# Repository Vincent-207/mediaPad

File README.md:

# mediaPad

This is my submission for hackpad. It's a macropad centered around media control, a mediaPad!
# Features
- 3 keyboard buttons
- One EC11 rotary encoder with a press button
- control of volume, pause/play, stop, skip forward, skip backward.

# PCB & Schematic

This was my first time using kiCAD or any PCB/Schematic design software.
It was unexpectedly pretty easy and the features were a lot more advanced that I was expecting. 

# CAD
This all fit's together with four m3 bolts & nuts that I will supply myself.

# BOM
- 1 XIAO RP2040
- 4x cherry mx red
- 4x DSA Keycaps
- 4x M3x16mm Bolts
- 4x M3 Nylock Nuts
- 1x EC11 Rotary Encoder
- 1x Case (2 3D printed parts)

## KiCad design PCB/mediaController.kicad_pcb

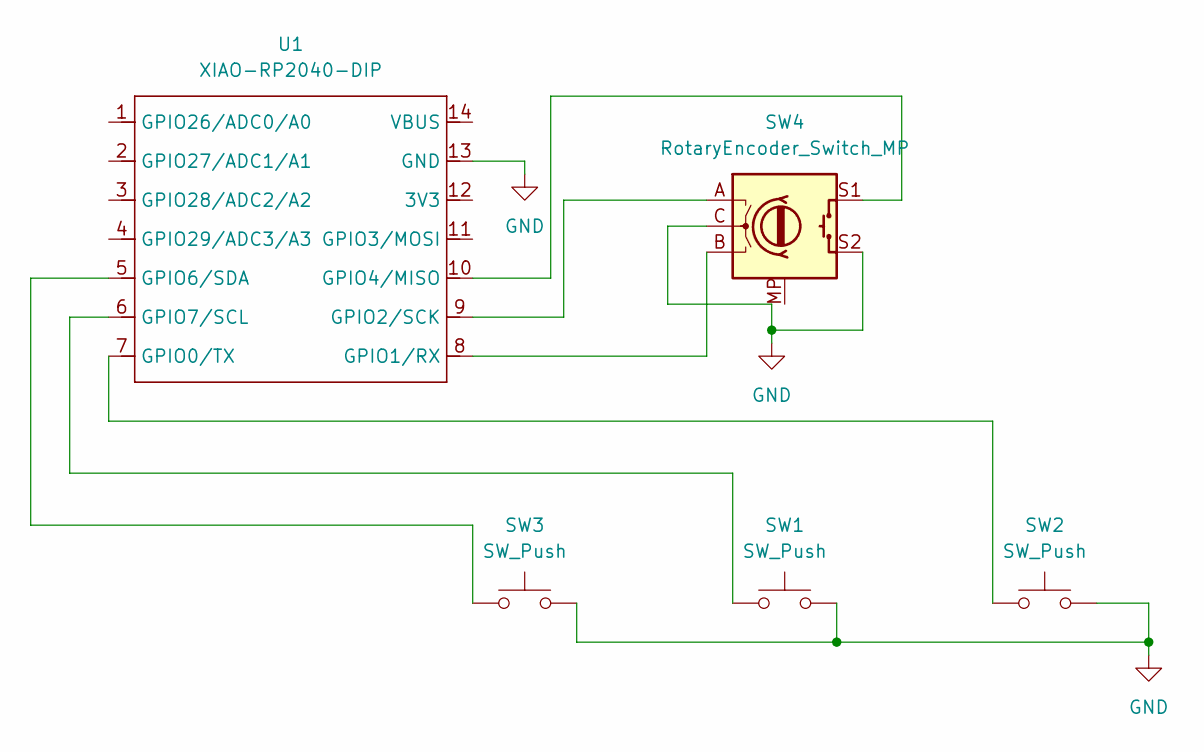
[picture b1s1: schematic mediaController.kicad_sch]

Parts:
SW1, SW2, SW3: SW_Push; SW_Cherry_MX_1.00u_PCB
SW4: RotaryEncoder_Switch_MP; RotaryEncoder_Alps_EC11E-Switch_Vertical_H20mm_MountingHoles
U1: XIAO-RP2040-DIP

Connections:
GND: SW1.2, SW2.2, SW3.2, SW4.C, SW4.S2, U1.13 (GND)
unnamed: SW2.1, U1.7 (GPIO0/TX)
unnamed: SW4.B, U1.8 (GPIO1/RX)
unnamed: SW4.A, U1.9 (GPIO2/SCK)
unnamed: SW4.S1, U1.10 (GPIO4/MISO)
unnamed: SW3.1, U1.5 (GPIO6/SDA)
unnamed: SW1.1, U1.6 (GPIO7/SCL)

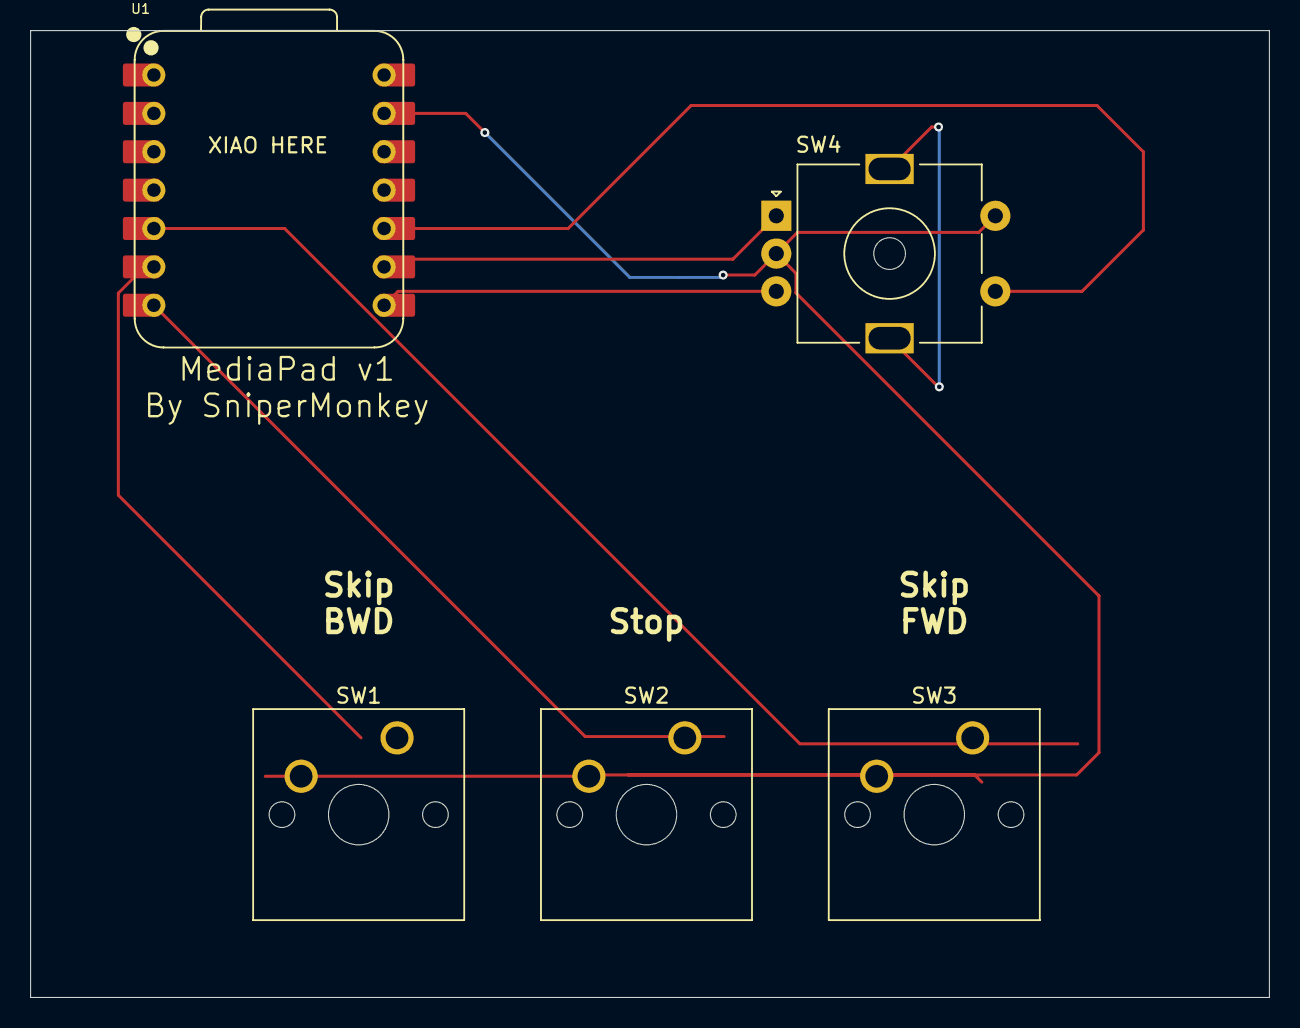
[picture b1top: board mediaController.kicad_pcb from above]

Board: 2 copper layers, 82.0 x 64.0 mm, 5 parts (0 on the bottom side), 7 nets.

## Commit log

2025-11-27 Import from previous
2025-11-27 First revision of firmware/hotkey code
2025-11-27 Cad Files
2025-11-27 PCB And firmware
2025-11-27 Readme details
2025-11-27 fixed full assembly picture
2025-11-27 update text
